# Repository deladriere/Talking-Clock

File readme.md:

Talking clock based on https://github.com/going-digital/Talkie 
# functions
* say time via push button (and IR hand detection on v2)
* update time via Ir remote (on V2)
* nap mode : alarm to sound after 25 minutes

# Todo
* publish v2 schematic
* publish v2 code
* publish casing openscad code
* add picture of casing
* check v1 for pcb error

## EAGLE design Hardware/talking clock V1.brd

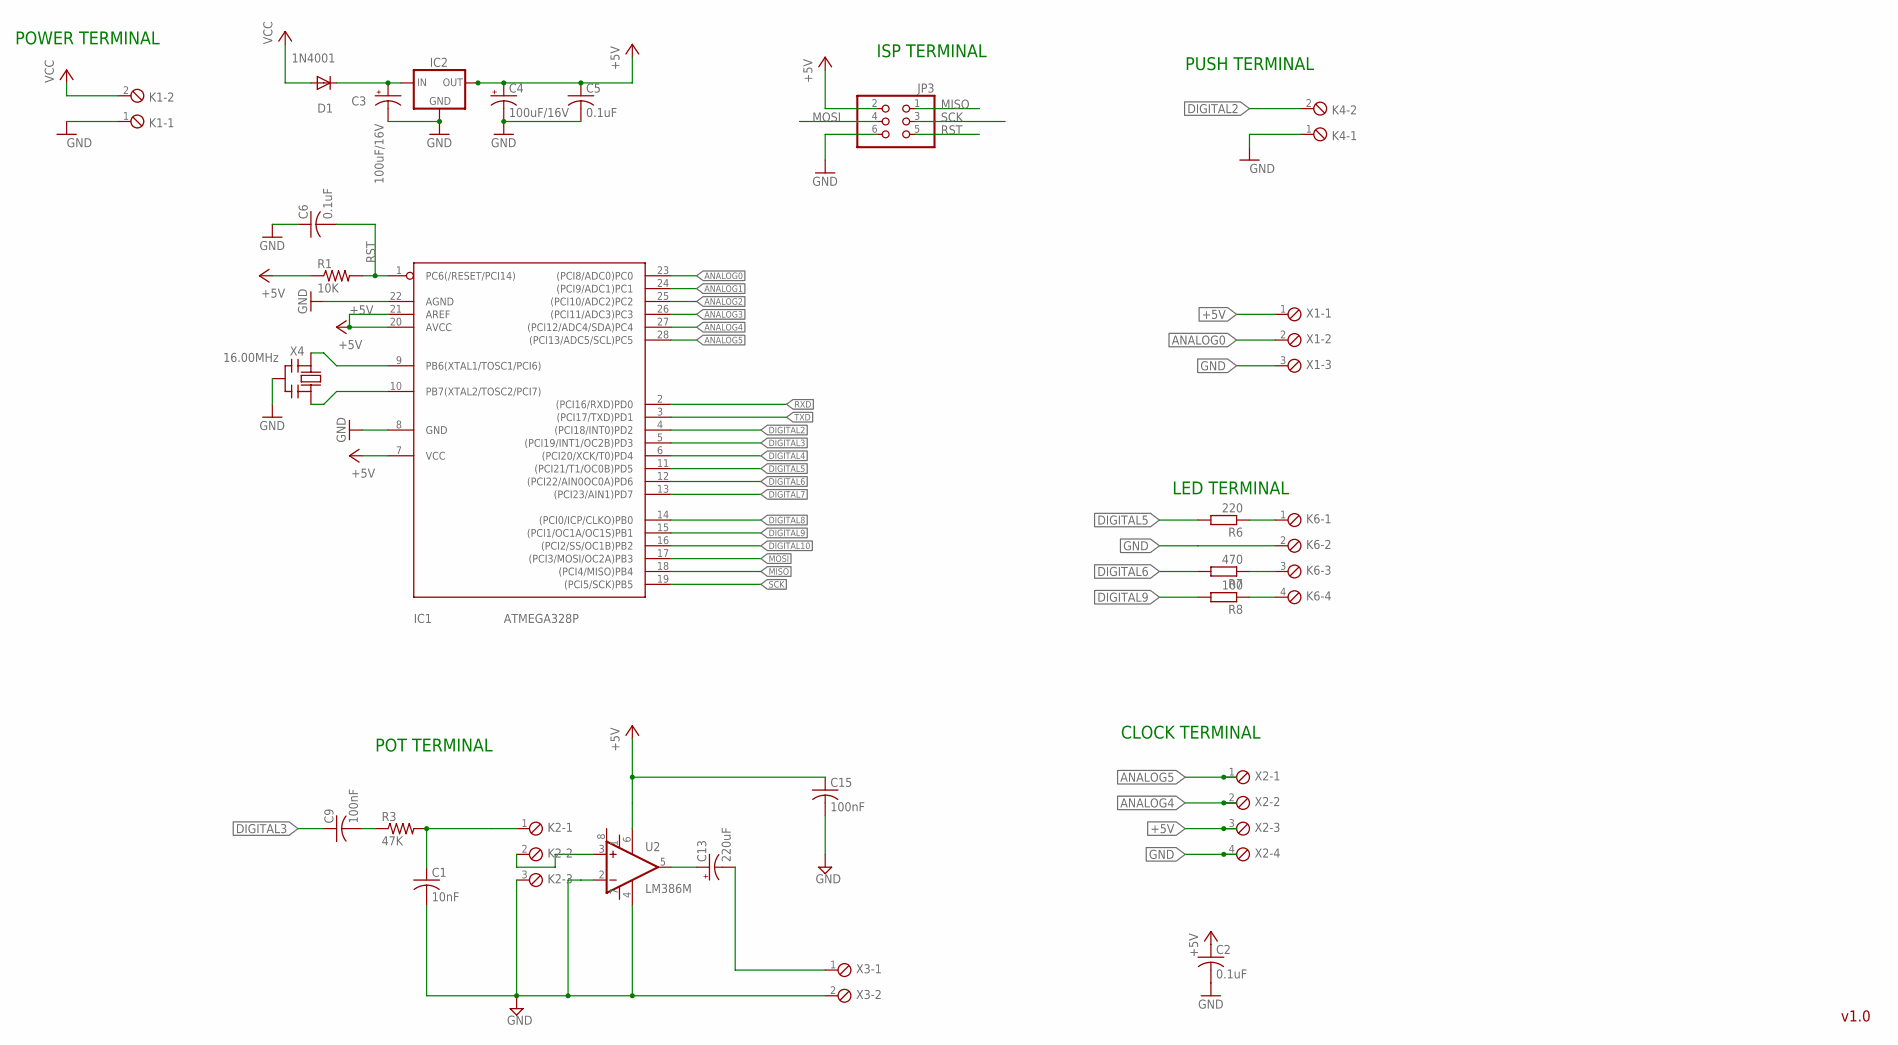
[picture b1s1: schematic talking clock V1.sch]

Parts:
C1: 10nF; C050-025X075
C2, C5, C6: 0.1uF; C025-025X050
C3, C4: 100uF/16V; E2,5-6
C9, C15: 100nF; C025-025X050
C13: 220uF; E3,5-10
D1: 1N4001; DO41-10
IC1: ATMEGA328P; DIL28/3
IC2: 78L05; 78XXS
JP3: PINHD-2X3; 2X03
K1, K4: MPT2; 2POL254
K2: MPT3; 3POL254
K6: MPT4; 4POL254
R1: 10K; 0207/10
R3: 47K; 0207/10
R6: 220; 0207/10
R7: 470; 0207/10
R8: 100; 0207/10
U2: LM386M; SO08
X1: MPT3; 3POL254
X2: MPT4; 4POL254
X3: MPT2; 2POL254
X4: 16.00MHz; CERM_OSC

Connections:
+5V: C2.1, C4.+, C5.1, C15.1, IC1.7 (VCC), IC1.20 (AVCC), IC1.21 (AREF), IC2.OUT, JP3.2, R1.1, U2.6 (V+), X1.1, X2.3
ANALOG0: IC1.23 ((PCI8/ADC0)PC0), X1.2
ANALOG1: IC1.24 ((PCI9/ADC1)PC1)
ANALOG2: IC1.25 ((PCI10/ADC2)PC2)
ANALOG3: IC1.26 ((PCI11/ADC3)PC3)
ANALOG4: IC1.27 ((PCI12/ADC4/SDA)PC4), X2.2
ANALOG5: IC1.28 ((PCI13/ADC5/SCL)PC5), X2.1
DIGITAL2: IC1.4 ((PCI18/INT0)PD2), K4.2
DIGITAL3: C9.1, IC1.5 ((PCI19/INT1/OC2B)PD3)
DIGITAL4: IC1.6 ((PCI20/XCK/T0)PD4)
DIGITAL5: IC1.11 ((PCI21/T1/OC0B)PD5), R6.2
DIGITAL6: IC1.12 ((PCI22/AIN0OC0A)PD6), R7.2
DIGITAL7: IC1.13 ((PCI23/AIN1)PD7)
DIGITAL8: IC1.14 ((PCI0/ICP/CLKO)PB0)
DIGITAL9: IC1.15 ((PCI1/OC1A/OC1S)PB1), R8.2
DIGITAL10: IC1.16 ((PCI2/SS/OC1B)PB2)
GND: C1.2, C2.2, C3.-, C4.-, C5.2, C6.1, C15.2, IC1.8 (GND), IC1.22 (AGND), IC2.GND, JP3.6, K1.1, K2.3, K4.1, K6.2, U2.2 (-IN), U2.4 (V-), X1.3, X2.4, X3.2, X4.P$2 (GND)
MISO: IC1.18 ((PCI4/MISO)PB4), JP3.1
MOSI: IC1.17 ((PCI3/MOSI/OC2A)PB3), JP3.4
unnamed: C13.-, X3.1
unnamed: K2.2, U2.3 (+IN)
unnamed: C3.+, D1.C, IC2.IN
unnamed: IC1.9 (PB6(XTAL1/TOSC1/PCI6)), X4.P$1 (IN)
unnamed: IC1.10 (PB7(XTAL2/TOSC2/PCI7)), X4.P$3 (OUT)
unnamed: K6.4, R8.1
unnamed: K6.3, R7.1
unnamed: K6.1, R6.1
unnamed: C9.2, R3.1
unnamed: C1.1, K2.1, R3.2
unnamed: C13.+, U2.5 (OUT)
RST: C6.2, IC1.1 (PC6(/RESET/PCI14)), JP3.5, R1.2
RXD: IC1.2 ((PCI16/RXD)PD0)
SCK: IC1.19 ((PCI5/SCK)PB5), JP3.3
TXD: IC1.3 ((PCI17/TXD)PD1)
VCC: D1.A, K1.2

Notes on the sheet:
v1.0
POWER TERMINAL
ISP TERMINAL
POT TERMINAL
LED TERMINAL
PUSH TERMINAL
CLOCK TERMINAL

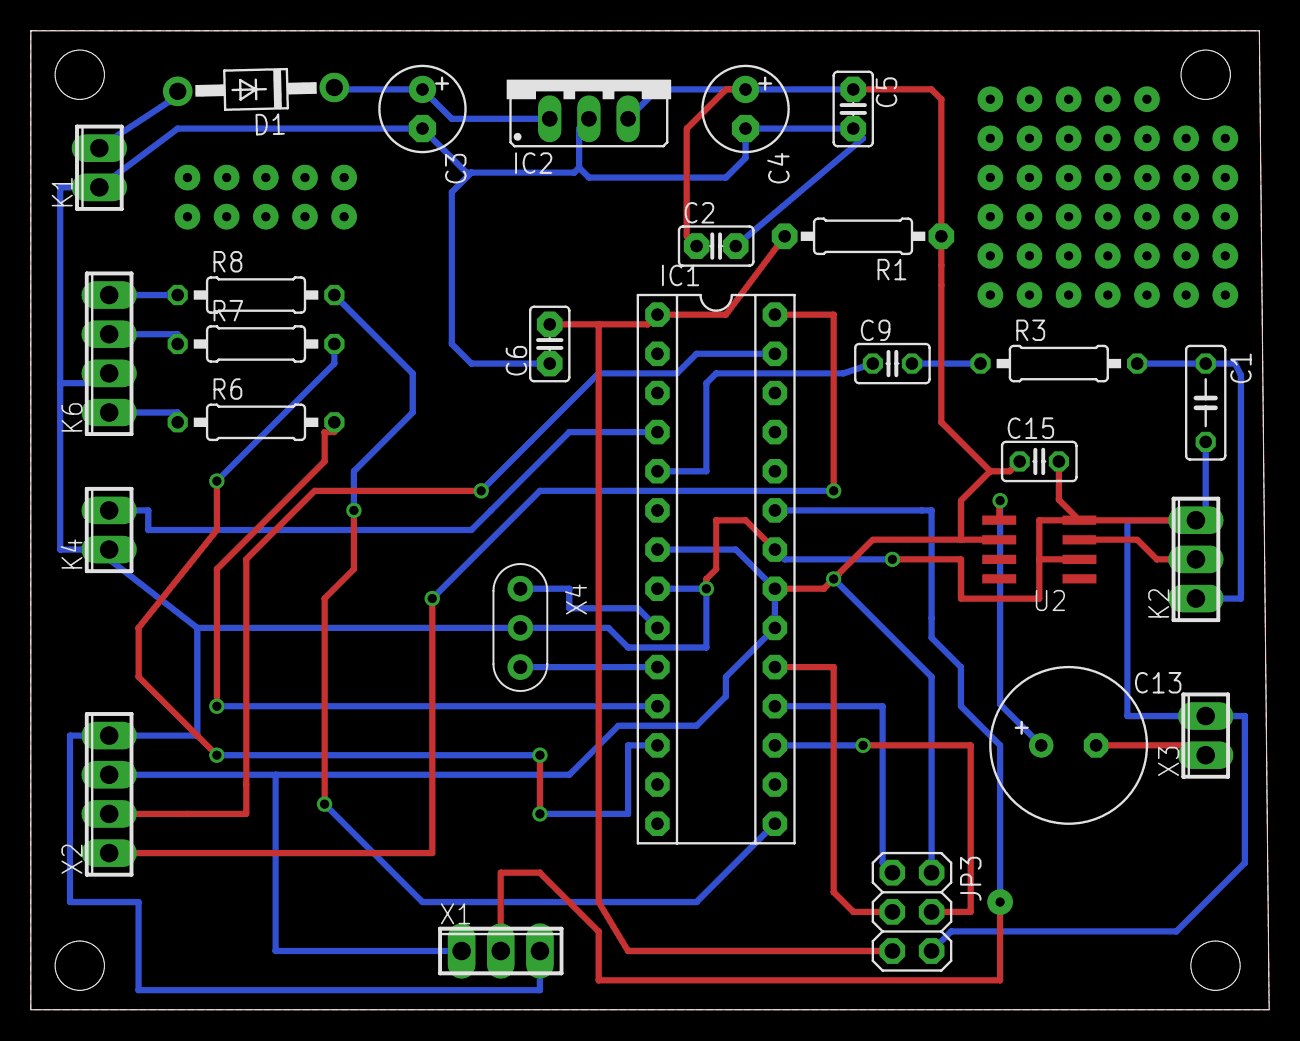
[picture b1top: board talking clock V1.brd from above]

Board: 2 copper layers, 80.3 x 63.5 mm, 27 parts (0 on the bottom side), 26 nets.

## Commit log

2014-03-10 First publication of project elements
    V1 of the talking clock
2014-03-10 Schematic added in png
2014-03-29 Update readme.md
    added a todo about the casing
2014-04-05 adding a line to the todo
2014-04-21 updating todo
2014-04-21 typo
2014-04-22 update todo
